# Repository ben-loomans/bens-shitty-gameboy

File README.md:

# bens-shitty-gameboy
Just like it says on the box: a pretty shitty "gameboy" that I learned a lot from making.

I made this repository after already finishing a working version of the BSG (Ben's Shitty "Gameboy"), because I think knowing how to use git and Github is valuable knowledge and learning within a context is far more effective than without.

Basic list of features (and their implementation status):
1.	6 hardware-debounced buttons (4 in a D-Pad arrangement + A & B)		Done
2.	A 128x64 LCD Screen													Done
3.	Light Dependent Resistor (LDR)										Done
4.	38kHz Infrared receiver												Done
5.	Infrared transmitter												Not Done
6.	Capacitive button													Not Done

Planned features will be added to a TODO document rather than here I think.

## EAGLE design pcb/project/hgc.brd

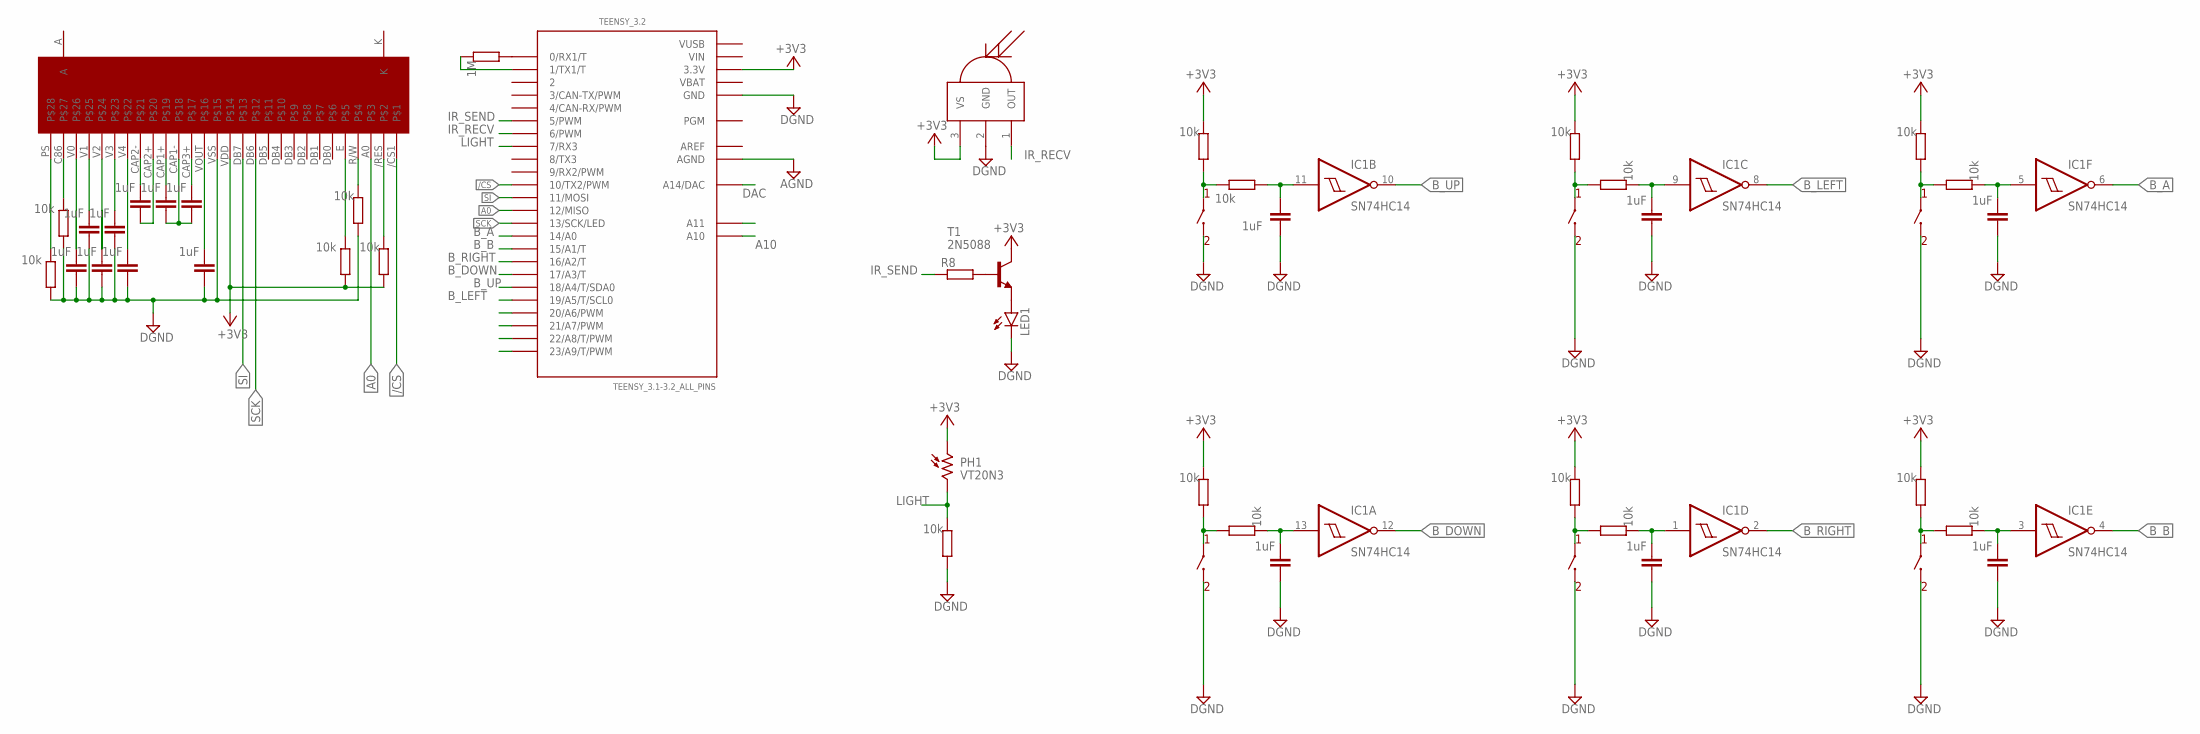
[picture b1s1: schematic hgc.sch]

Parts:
A: TACTILE_SWITCH; SPST-NO
B: TACTILE_SWITCH; SPST-NO
C1, C2, C3, C4, C5, C6, C7, C8, C9, C10, C11, C12, C13, C14, C15: 1uF; C0603
DOWN: TACTILE_SWITCH; SPST-NO
IC1: SN74HC14; SO14
LED1: LED3MM
LEFT: TACTILE_SWITCH; SPST-NO
PH1: VT20N3; TO46-VT200
R1, R2, R3, R4, R5, R6, R7, R9, R10, R11, R12, R13, R15, R16, R18, R19, R21, R22: 10k; R0603
R8: R-EU_0204/7; 0204/7
R14: 1M; R0603
RIGHT: TACTILE_SWITCH; SPST-NO
T1: 2N5088; TO92
TEENSY_3.2: TEENSY_3.1-3.2_ALL_PINS; TEENSY_3.0-3.2&LC_ALL_PINS
U$2: LCD_DISPLAY; LCD_SCREEN
U$3: IR_RECEIVER; T-30_V
UP: TACTILE_SWITCH; SPST-NO

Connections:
20: TEENSY_3.2.20/A6 (20/A6/PWM)
21: TEENSY_3.2.21/A7 (21/A7/PWM)
22: TEENSY_3.2.22/A8 (22/A8/T/PWM)
23: TEENSY_3.2.23/A9 (23/A9/T/PWM)
/CS: TEENSY_3.2.10 (10/TX2/PWM), U$2./CS1
/WRITE: R2.1, U$2.R/W
A: U$2.A
A0: TEENSY_3.2.12 (12/MISO), U$2.A0
A10: TEENSY_3.2.A10
A11: TEENSY_3.2.A11
AGND: TEENSY_3.2.AGND
AREF: TEENSY_3.2.AREF
B_A: IC1.6 (O), TEENSY_3.2.14/A0
B_B: IC1.4 (O), TEENSY_3.2.15/A1 (15/A1/T)
B_DOWN: IC1.12 (O), TEENSY_3.2.17/A3 (17/A3/T)
B_LEFT: IC1.8 (O), TEENSY_3.2.19/A5 (19/A5/T/SCL0)
B_RIGHT: IC1.2 (O), TEENSY_3.2.16/A2 (16/A2/T)
B_UP: IC1.10 (O), TEENSY_3.2.18/A4 (18/A4/T/SDA0)
DAC: TEENSY_3.2.RESET/DAC (A14/DAC)
DGND: A.3 (2), A.4 (2), B.3 (2), B.4 (2), C1.2, C2.2, C3.2, C4.2, C5.2, C9.2, C10.2, C11.2, C12.2, C13.2, C14.2, C15.2, DOWN.3 (2), DOWN.4 (2), IC1.7 (GND), LED1.K (C), LEFT.3 (2), LEFT.4 (2), R2.2, R4.1, R5.1, R11.2, RIGHT.3 (2), RIGHT.4 (2), TEENSY_3.2.GND, TEENSY_3.2.GND1 (GND), U$2.VSS, U$3.2 (GND), UP.3 (2), UP.4 (2)
ENABLE: R1.2, U$2.E
IR_RECV: TEENSY_3.2.6 (6/PWM), U$3.1 (OUT)
IR_SEND: R8.1, TEENSY_3.2.5 (5/PWM)
K: U$2.K
LIGHT: PH1.2, R11.1, TEENSY_3.2.7 (7/RX3)
unnamed: C1.1, U$2.V0
unnamed: C2.1, U$2.V1
unnamed: C3.1, U$2.V2
unnamed: C4.1, U$2.V3
unnamed: C5.1, U$2.V4
unnamed: C6.1, U$2.CAP2-
unnamed: C7.1, U$2.CAP1+
unnamed: C8.1, U$2.CAP3+
unnamed: C9.1, U$2.VOUT
unnamed: R3.1, U$2./RES
unnamed: C6.2, U$2.CAP2+
unnamed: C7.2, C8.2, U$2.CAP1-
unnamed: R4.2, U$2.PS
unnamed: R5.2, U$2.C86
unnamed: LED1.A, T1.3 (E)
unnamed: R6.2, R7.2, UP.1, UP.2 (1)
unnamed: C10.1, IC1.11 (I), R7.1
unnamed: LEFT.1, LEFT.2 (1), R9.2, R10.2
unnamed: R8.2, T1.2 (B)
unnamed: C11.1, IC1.9 (I), R10.1
unnamed: A.1, A.2 (1), R12.2, R13.2
unnamed: C12.1, IC1.5 (I), R13.1
unnamed: DOWN.1, DOWN.2 (1), R15.2, R16.2
unnamed: R14.2, TEENSY_3.2.0 (0/RX1/T)
unnamed: C13.1, IC1.13 (I), R16.1
unnamed: R18.2, R19.2, RIGHT.1, RIGHT.2 (1)
unnamed: R14.1, TEENSY_3.2.1 (1/TX1/T)
unnamed: C14.1, IC1.1 (I), R19.1
unnamed: B.1, B.2 (1), R21.2, R22.2
unnamed: C15.1, IC1.3 (I), R22.1
SCK: TEENSY_3.2.13 (13/SCK/LED), U$2.DB6
SI: TEENSY_3.2.11 (11/MOSI), U$2.DB7
VBAT: TEENSY_3.2.VBAT
VCC: IC1.14 (VCC), PH1.1, R1.1, R3.2, R6.1, R9.1, R12.1, R15.1, R18.1, R21.1, T1.1 (C), TEENSY_3.2.3.3V, TEENSY_3.2.3.3V1 (3.3V), U$2.VDD, U$3.3 (VS)
VIN: TEENSY_3.2.VIN
VUSB: TEENSY_3.2.VUSB

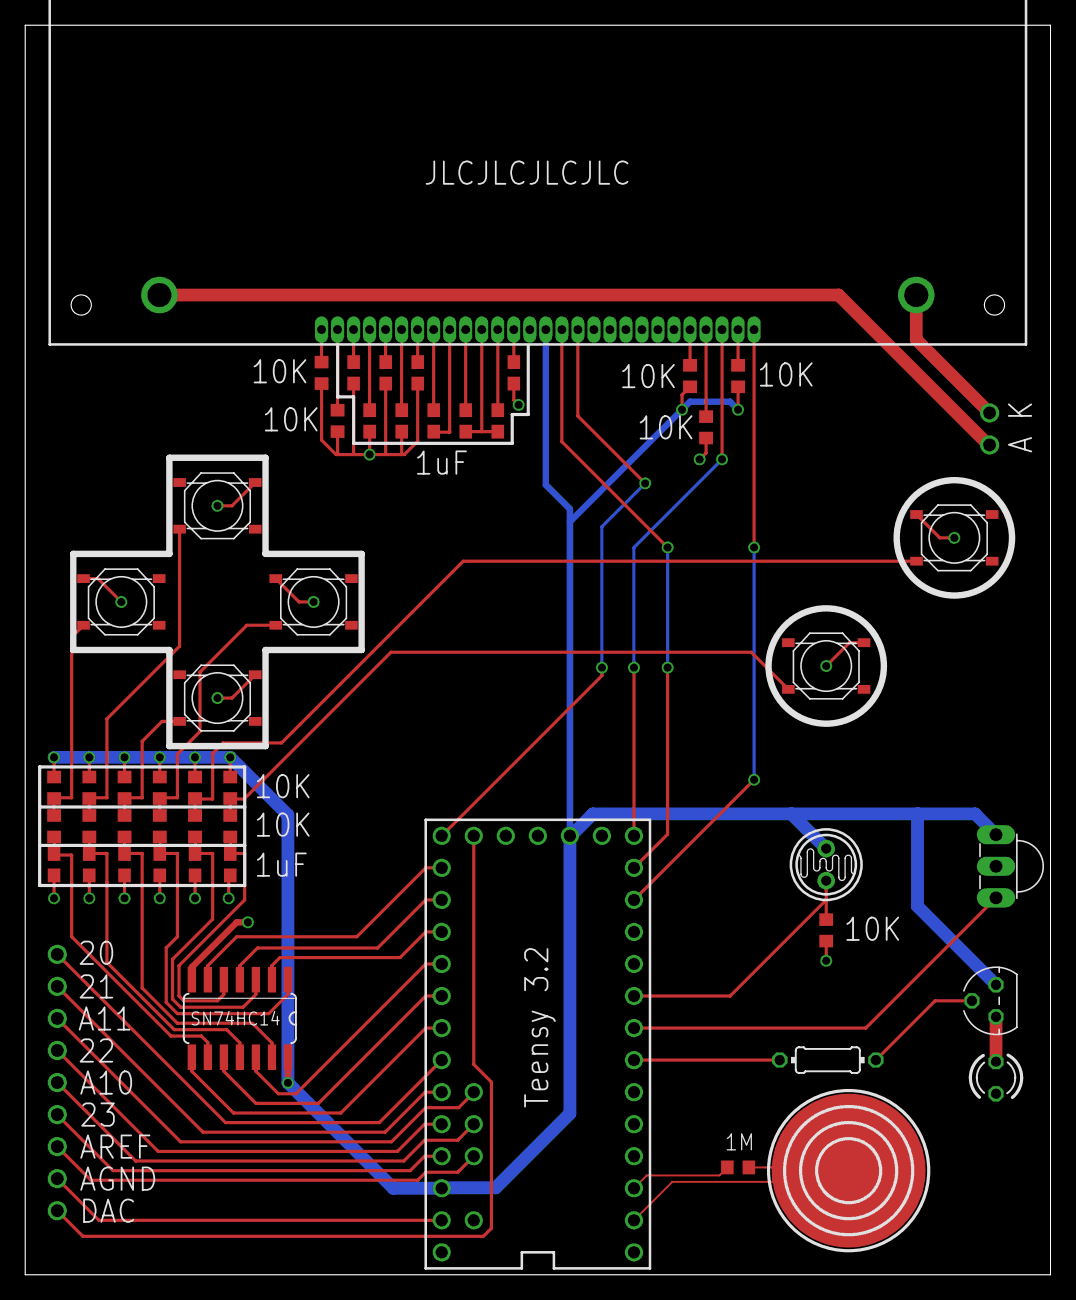
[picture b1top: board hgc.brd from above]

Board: 2 copper layers, 81.3 x 99.1 mm, 48 parts (0 on the bottom side), 47 nets.

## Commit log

2020-01-31 Add Arduino code
2020-01-31 Add datasheets and resources
2020-01-31 Add pcb-related files
2020-01-31 Create TODO.md
    Ideas off the top of my head for how to improve the next iteration
2020-02-08 start asteroid game
2020-02-08 .DS_Store banished
2020-02-09 change char to uint8_t and add rudimentary button function stack
